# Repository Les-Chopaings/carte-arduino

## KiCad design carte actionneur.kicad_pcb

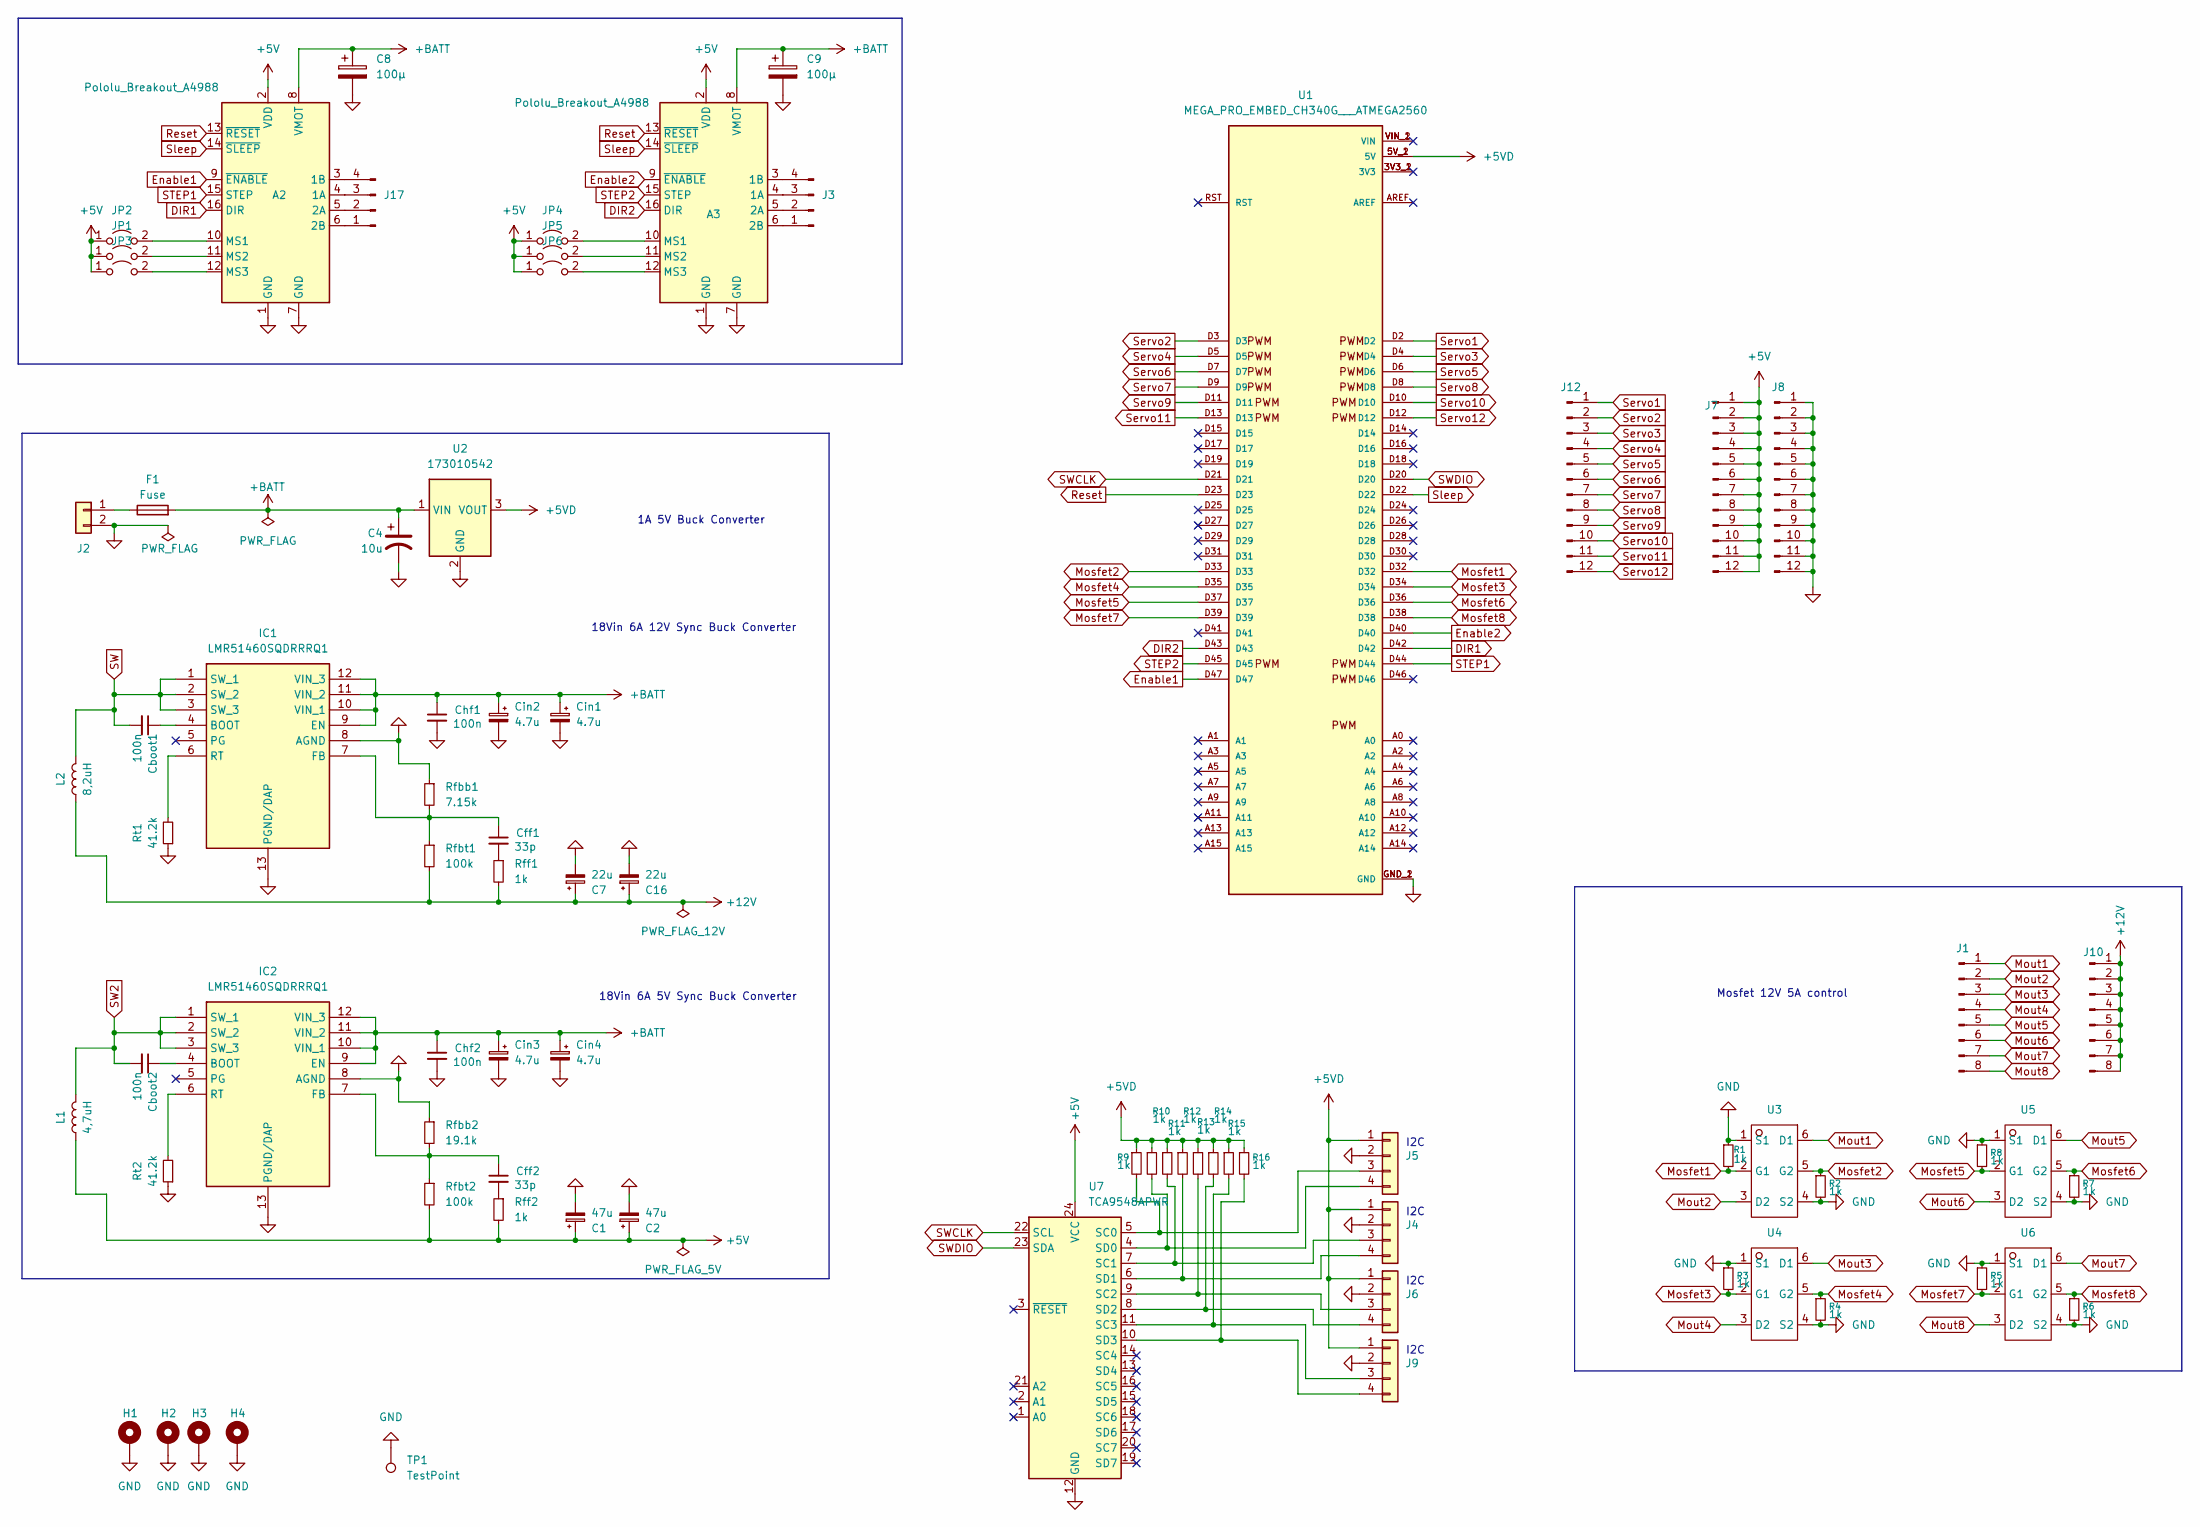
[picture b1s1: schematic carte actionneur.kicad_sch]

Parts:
A2, A3: Pololu_Breakout_A4988; Pololu_Breakout-16_15.2x20.3mm
C1, C2: 47u; C_1206_3216Metric
C4: 10u; C_1206_3216Metric
C7, C16: 22u; C_1206_3216Metric
C8, C9: 100µ; CP_Radial_D8.0mm_P3.50mm
Cboot1, Cboot2: 100n; C_1206_3216Metric
Cff1, Cff2: 33p; C_1206_3216Metric
Chf1, Chf2: 100n; C_1206_3216Metric
Cin1, Cin2, Cin3, Cin4: 4.7u; C_1206_3216Metric
F1: Fuse; Fuseholder_Cylinder-5x20mm_EATON_H15-V-1_Vertical_Closed
H1, H2, H3, H4: MountingHole_Pad; MountingHole_3.2mm_M3_Pad_Via
IC1, IC2: LMR51460SQDRRRQ1; SON50P300X300X80-13N-D; Manufacturer_Part_Number LMR51460SQDRRRQ1
J1, J10: Conn_01x08_Pin; PinHeader_1x08_P2.54mm_Vertical
J2: Conn_01x02; CUI_TBP01R1-508-02BE
J3, J17: Conn_01x04_Pin; JST_XH_B4B-XH-A_1x04_P2.50mm_Vertical
J4, J5, J6, J9: Conn_01x03; PinHeader_1x04_P2.54mm_Vertical
J7, J8, J12: Conn_01x12_Pin; PinHeader_1x12_P2.54mm_Vertical
JP1, JP2, JP3, JP4, JP5, JP6: Jumper_2_Open; SolderJumper-2_P1.3mm_Open_TrianglePad1.0x1.5mm
L1: 4,7uH; INDPM7168X300N
L2: 8,2uH; INDPM7168X300N
R1, R2, R3, R4, R5, R6, R7, R8, R9, R10, R11, R12, R13, R14, R15, R16: 1k; R_1206_3216Metric
Rfbb1: 7.15k; R_1206_3216Metric
Rfbb2: 19.1k; R_1206_3216Metric
Rfbt1, Rfbt2: 100k; R_1206_3216Metric
Rff1, Rff2: 1k; R_1206_3216Metric
Rt1, Rt2: 41.2k; R_1206_3216Metric
TP1: TestPoint; TestPoint_Bridge_Pitch2.0mm_Drill0.7mm
U1: MEGA_PRO_EMBED_CH340G___ATMEGA2560; MODULE_MEGA_PRO_2_CONNECTOR; PARTREV 12/May/2017
U2: 173010542; U_Wurth_MagIC-FDSM_173010x42
U3, U4, U5, U6: TSOP-6_1.65x3.05mm_P0.95mm
U7: TCA9548APWR; ADA Perso

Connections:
+5V: A2.2 (VDD), A3.2 (VDD), C1.1, C2.1, J7.1, J7.2, J7.3, J7.4, J7.5, J7.6, J7.7, J7.8, J7.9, J7.10, J7.11, J7.12, JP1.1 (A), JP2.1 (A), JP3.1 (A), JP4.1 (A), JP5.1 (A), JP6.1 (A), L1.2, Rfbt2.2, Rff2.2, U7.24 (VCC)
+5VD: J4.1, J5.1, J6.1, J9.1, R9.1, R10.1, R11.1, R12.1, R13.1, R14.1, R15.1, R16.1, U1.5V_1 (5V), U1.5V_2 (5V), U2.3 (VOUT)
+12V: C7.1, C16.1, J10.1, J10.2, J10.3, J10.4, J10.5, J10.6, J10.7, J10.8, L2.2, Rfbt1.2, Rff1.2
+BATT: A2.8 (VMOT), A3.8 (VMOT), C4.1, C8.1, C9.1, Chf1.1, Chf2.1, Cin1.1, Cin2.1, Cin3.1, Cin4.1, F1.2, IC1.9 (EN), IC1.10 (VIN_1), IC1.11 (VIN_2), IC1.12 (VIN_3), IC2.9 (EN), IC2.10 (VIN_1), IC2.11 (VIN_2), IC2.12 (VIN_3), U2.1 (VIN)
DIR1: A2.16 (DIR), U1.D42
DIR2: A3.16 (DIR), U1.D43
Enable1: A2.9 (~ENABLE), U1.D47
Enable2: A3.9 (~ENABLE), U1.D40
GND: A2.1 (GND), A2.7 (GND), A3.1 (GND), A3.7 (GND), C1.2, C2.2, C4.2, C7.2, C8.2, C9.2, C16.2, Chf1.2, Chf2.2, Cin1.2, Cin2.2, Cin3.2, Cin4.2, H1.1, H2.1, H3.1, H4.1, IC1.8 (AGND), IC1.13 (PGND/DAP), IC2.8 (AGND), IC2.13 (PGND/DAP), J2.2, J4.2, J5.2, J6.2, J8.1, J8.2, J8.3, J8.4, J8.5, J8.6, J8.7, J8.8, J8.9, J8.10, J8.11, J8.12, J9.2, R1.1, R2.2, R3.1, R4.2, R5.1, R6.2, R7.2, R8.1, Rfbb1.1, Rfbb2.1, Rt1.1, Rt2.1, TP1.1, U1.GND_1 (GND), U1.GND_2 (GND), U2.2 (GND), U3.1 (S1), U3.4 (S2), U4.1 (S1), U4.4 (S2), U5.1 (S1), U5.4 (S2), U6.1 (S1), U6.4 (S2), U7.12 (GND)
Mosfet1: R1.2, U1.D32, U3.2 (G1)
Mosfet2: R2.1, U1.D33, U3.5 (G2)
Mosfet3: R3.2, U1.D34, U4.2 (G1)
Mosfet4: R4.1, U1.D35, U4.5 (G2)
Mosfet5: R8.2, U1.D37, U5.2 (G1)
Mosfet6: R7.1, U1.D36, U5.5 (G2)
Mosfet7: R5.2, U1.D39, U6.2 (G1)
Mosfet8: R6.1, U1.D38, U6.5 (G2)
Mout1: J1.1, U3.6 (D1)
Mout2: J1.2, U3.3 (D2)
Mout3: J1.3, U4.6 (D1)
Mout4: J1.4, U4.3 (D2)
Mout5: J1.5, U5.6 (D1)
Mout6: J1.6, U5.3 (D2)
Mout7: J1.7, U6.6 (D1)
Mout8: J1.8, U6.3 (D2)
unnamed: A2.4 (1A), J17.3
unnamed: A2.3 (1B), J17.4
unnamed: A2.5 (2A), J17.2
unnamed: A2.6 (2B), J17.1
unnamed: A2.10 (MS1), JP2.2 (B)
unnamed: A2.11 (MS2), JP1.2 (B)
unnamed: A2.12 (MS3), JP3.2 (B)
unnamed: A3.4 (1A), J3.3
unnamed: A3.3 (1B), J3.4
unnamed: A3.5 (2A), J3.2
unnamed: A3.6 (2B), J3.1
unnamed: A3.10 (MS1), JP4.2 (B)
unnamed: A3.11 (MS2), JP5.2 (B)
unnamed: A3.12 (MS3), JP6.2 (B)
unnamed: Cff1.2, Rff1.1
unnamed: Cff2.2, Rff2.1
unnamed: Cboot1.1, IC1.4 (BOOT)
unnamed: Cff1.1, IC1.7 (FB), Rfbb1.2, Rfbt1.1
unnamed: IC1.6 (RT), Rt1.2
unnamed: Cboot2.1, IC2.4 (BOOT)
unnamed: Cff2.1, IC2.7 (FB), Rfbb2.2, Rfbt2.1
unnamed: IC2.6 (RT), Rt2.2
unnamed: F1.1, J2.1
unnamed: J4.3, R11.2, U7.7 (SC1)
unnamed: J4.4, R12.2, U7.6 (SD1)
unnamed: J5.3, R9.2, U7.5 (SC0)
unnamed: J5.4, R10.2, U7.4 (SD0)
unnamed: J6.3, R13.2, U7.9 (SC2)
unnamed: J6.4, R14.2, U7.8 (SD2)
unnamed: J9.3, R15.2, U7.11 (SC3)
unnamed: J9.4, R16.2, U7.10 (SD3)
Reset: A2.13 (~RESET), A3.13 (~RESET), U1.D23
STEP1: A2.15 (STEP), U1.D44
STEP2: A3.15 (STEP), U1.D45
SW: Cboot1.2, IC1.1 (SW_1), IC1.2 (SW_2), IC1.3 (SW_3), L2.1
SW2: Cboot2.2, IC2.1 (SW_1), IC2.2 (SW_2), IC2.3 (SW_3), L1.1
SWCLK: U1.D21, U7.22 (SCL)
SWDIO: U1.D20, U7.23 (SDA)
Servo1: J12.1, U1.D2
Servo2: J12.2, U1.D3
Servo3: J12.3, U1.D4
Servo4: J12.4, U1.D5
Servo5: J12.5, U1.D6
Servo6: J12.6, U1.D7
Servo7: J12.7, U1.D9
Servo8: J12.8, U1.D8
Servo9: J12.9, U1.D11
Servo10: J12.10, U1.D10
Servo11: J12.11, U1.D13
Servo12: J12.12, U1.D12
Sleep: A2.14 (~SLEEP), A3.14 (~SLEEP), U1.D22

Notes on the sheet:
18Vin 6A 5V Sync Buck Converter
Mosfet 12V 5A control
18Vin 6A 12V Sync Buck Converter
I2C
1A 5V Buck Converter

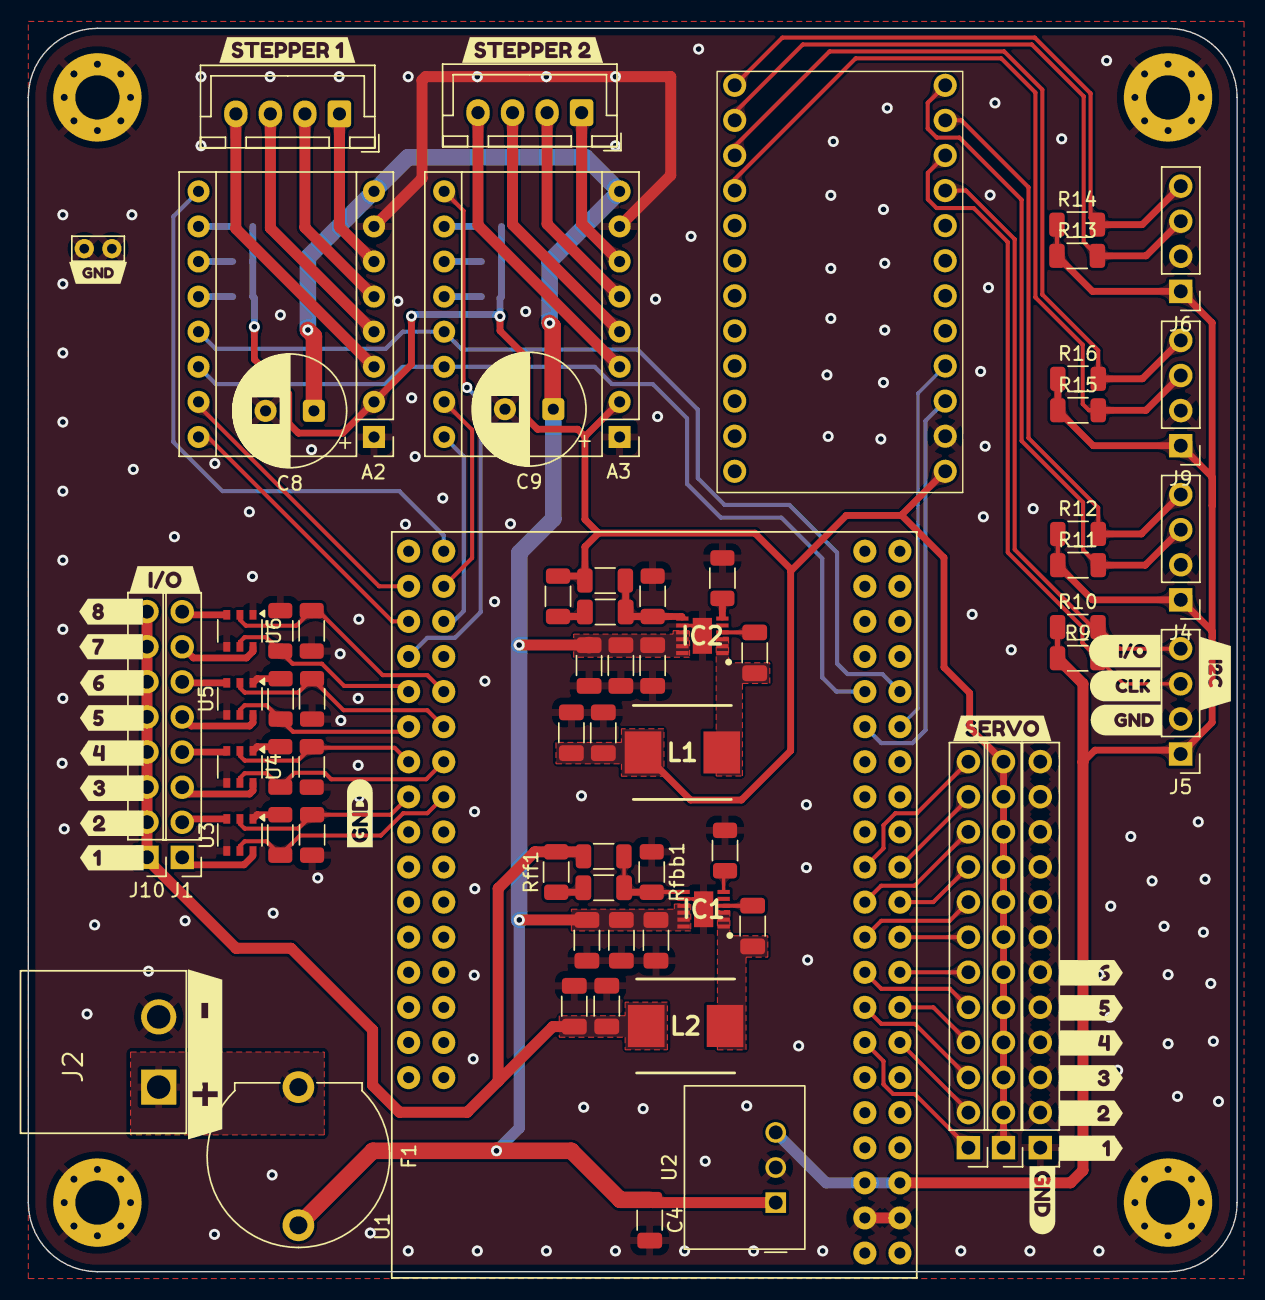
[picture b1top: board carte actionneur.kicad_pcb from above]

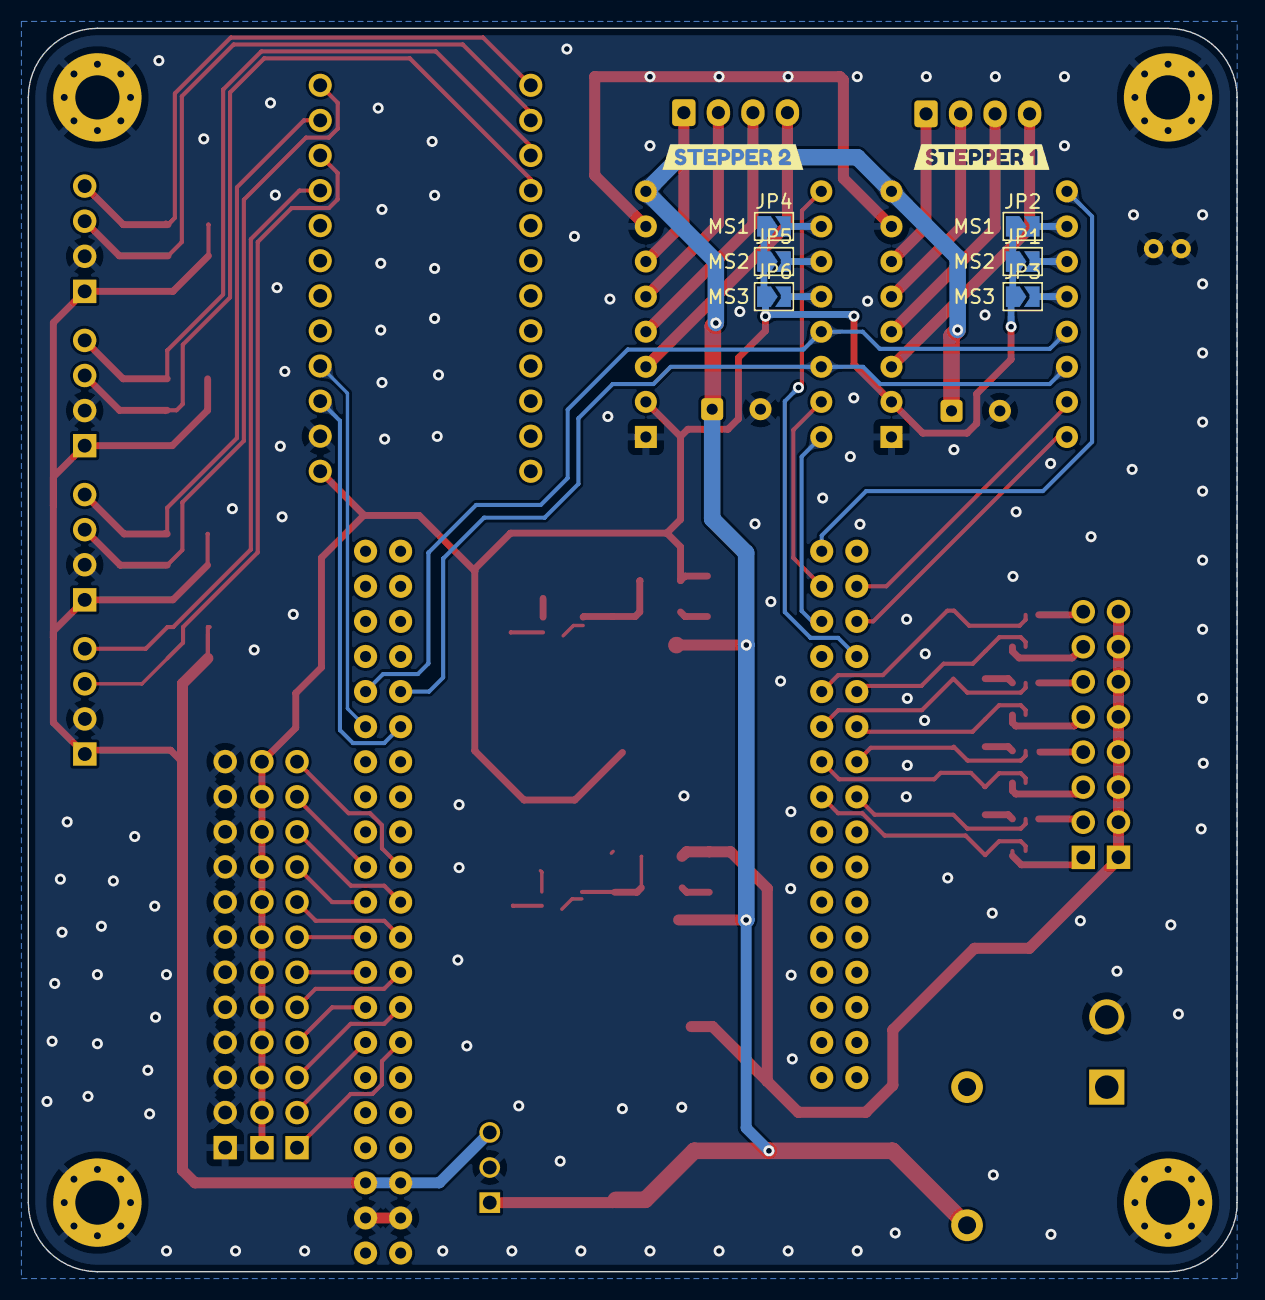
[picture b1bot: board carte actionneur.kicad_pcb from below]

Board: 2 copper layers, 87.5 x 90.0 mm, 106 parts (8 on the bottom side), 76 nets.

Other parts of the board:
kibuzzard-67A0F0A3: G***; kibuzzard-67A0F0A3
kibuzzard-67A0F0D2: G***; kibuzzard-67A0F0D2
kibuzzard-67A0F0E8: G***; kibuzzard-67A0F0E8
kibuzzard-67A0F0EE: G***; kibuzzard-67A0F0EE
kibuzzard-67A13B87: G***; kibuzzard-67A13B87
kibuzzard-67A14542: G***; kibuzzard-67A14542
kibuzzard-679EA1D9: G***; kibuzzard-679EA1D9
kibuzzard-679EA1F0: G***; kibuzzard-679EA1F0
kibuzzard-679EA1FA: G***; kibuzzard-679EA1FA
kibuzzard-679EA20F: G***; kibuzzard-679EA20F
kibuzzard-679EA25C: G***; kibuzzard-679EA25C
kibuzzard-679EA204: G***; kibuzzard-679EA204
kibuzzard-679EA208: G***; kibuzzard-679EA208
kibuzzard-679EA236, kibuzzard-679EA236#2: G***; kibuzzard-679EA236
kibuzzard-679FD2F5: G***; kibuzzard-679FD2F5
kibuzzard-679FD63B: G***; kibuzzard-679FD63B
kibuzzard-679FD63E: G***; kibuzzard-679FD63E
kibuzzard-679FD64B: G***; kibuzzard-679FD64B
kibuzzard-679FD326: G***; kibuzzard-679FD326
kibuzzard-679FD606: G***; kibuzzard-679FD606
kibuzzard-679FD637: G***; kibuzzard-679FD637
kibuzzard-679FD642: G***; kibuzzard-679FD642
kibuzzard-679FD645: G***; kibuzzard-679FD645
kibuzzard-679FD648: G***; kibuzzard-679FD648
kibuzzard-679FD690: G***; kibuzzard-679FD690
kibuzzard-679FDC70: G***; kibuzzard-679FDC70
kibuzzard-679FDCB9: G***; kibuzzard-679FDCB9

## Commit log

2025-10-14 - Added 3 servo pin, for a total of 12 // - Modified pin assignment to connect to proper PWM arduino pins // - Added pull-down resistors to mosfets // - Deleted PWM lidar pin // - Modified inductor c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
2025-11-11 Added TCA9548A module for I2C multiplexing
2025-11-11 Modified pins and added 5V to I2C
2025-11-15 fix warning pcb
2025-11-16 Modified fuse holder footprint
